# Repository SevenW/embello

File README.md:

Embedded software from JeeLabs
==============================

Quick Links
-----------

* [Home page and docs](http://embello.jeelabs.org/)
* [Forth-based JeeLabs JeeNodes Zero](./explore/1608-forth)

Acknowledgments
---------------

With many thanks for the inspiring discussions and code contributions by:

* James Churchill
* Thorsten von Eicken
* Martyn Judd
* Matthias Koch
* Thomas Lohmüller
* John O'Hare
* Joris Pragt
* Frank (SevenW)
* Matthias Ulrich

-- [jcw](http://jeelabs.org/about/)

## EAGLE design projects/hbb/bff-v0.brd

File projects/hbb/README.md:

See <http://jeelabs.org/2016/01/arduino-shields...-or-not/>

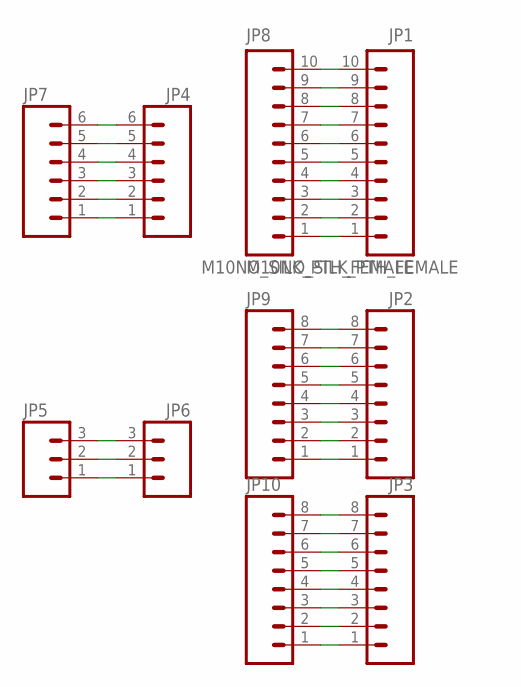
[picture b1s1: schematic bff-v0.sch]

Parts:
JP1, JP8: M10NO_SILK_PTH_FEMALE; 1X10_NO_SILK
JP2, JP3, JP9, JP10: M08NO_SILK_FEMALE_PTH; 1X08_NO_SILK
JP4, JP7: M06NO_SILK_FEMALE_PTH; 1X06_NO_SILK
JP5: M03LOCK_NO_SILK; 1X03_LOCK_NO_SILK
JP6: M03PTH; 1X03

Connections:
unnamed: JP5.1, JP6.1
unnamed: JP5.2, JP6.2
unnamed: JP5.3, JP6.3
unnamed: JP4.1, JP7.1
unnamed: JP4.2, JP7.2
unnamed: JP4.3, JP7.3
unnamed: JP4.4, JP7.4
unnamed: JP4.5, JP7.5
unnamed: JP4.6, JP7.6
unnamed: JP1.1, JP8.1
unnamed: JP1.2, JP8.2
unnamed: JP1.3, JP8.3
unnamed: JP1.4, JP8.4
unnamed: JP1.5, JP8.5
unnamed: JP1.6, JP8.6
unnamed: JP1.7, JP8.7
unnamed: JP1.8, JP8.8
unnamed: JP1.9, JP8.9
unnamed: JP1.10, JP8.10
unnamed: JP2.1, JP9.1
unnamed: JP2.2, JP9.2
unnamed: JP2.3, JP9.3
unnamed: JP2.4, JP9.4
unnamed: JP2.5, JP9.5
unnamed: JP2.6, JP9.6
unnamed: JP2.7, JP9.7
unnamed: JP2.8, JP9.8
unnamed: JP3.1, JP10.1
unnamed: JP3.2, JP10.2
unnamed: JP3.3, JP10.3
unnamed: JP3.4, JP10.4
unnamed: JP3.5, JP10.5
unnamed: JP3.6, JP10.6
unnamed: JP3.7, JP10.7
unnamed: JP3.8, JP10.8

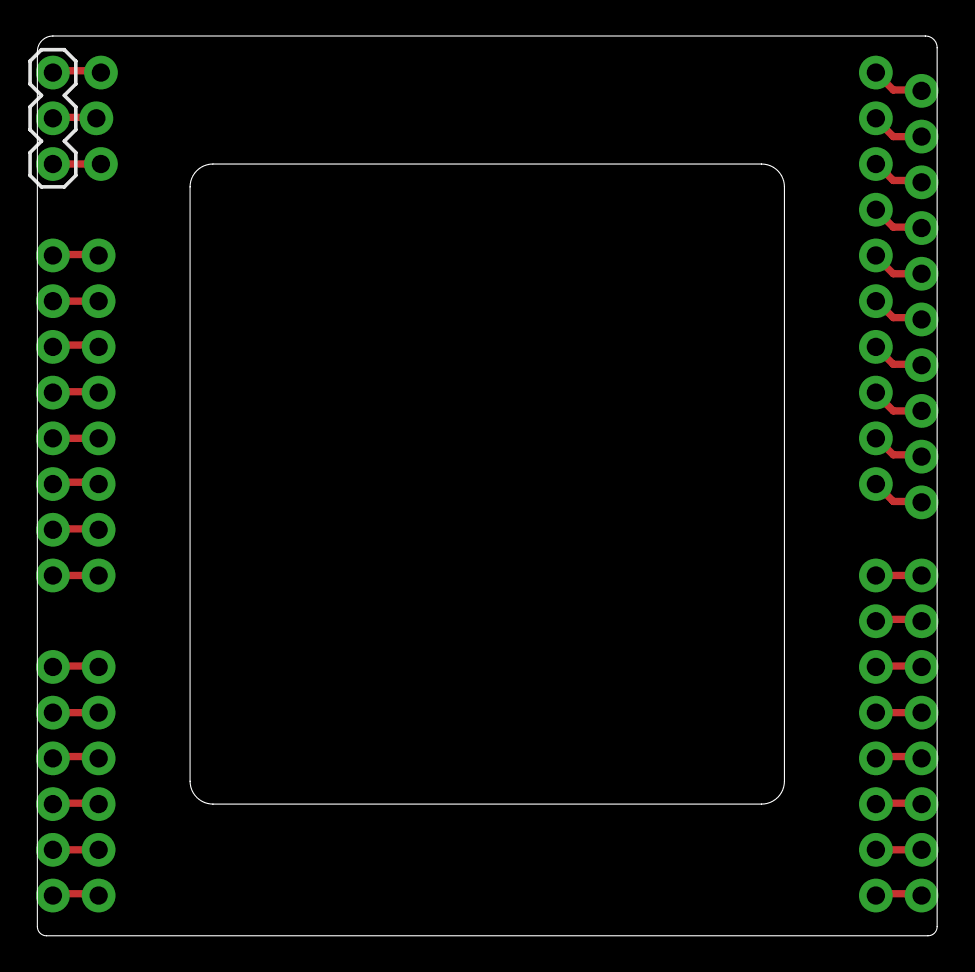
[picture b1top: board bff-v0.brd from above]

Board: 2 copper layers, 50.0 x 50.0 mm, 10 parts (0 on the bottom side), 35 nets.

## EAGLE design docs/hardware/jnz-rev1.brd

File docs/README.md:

This documentation can be viewed at <http://embello.jeelabs.org>.

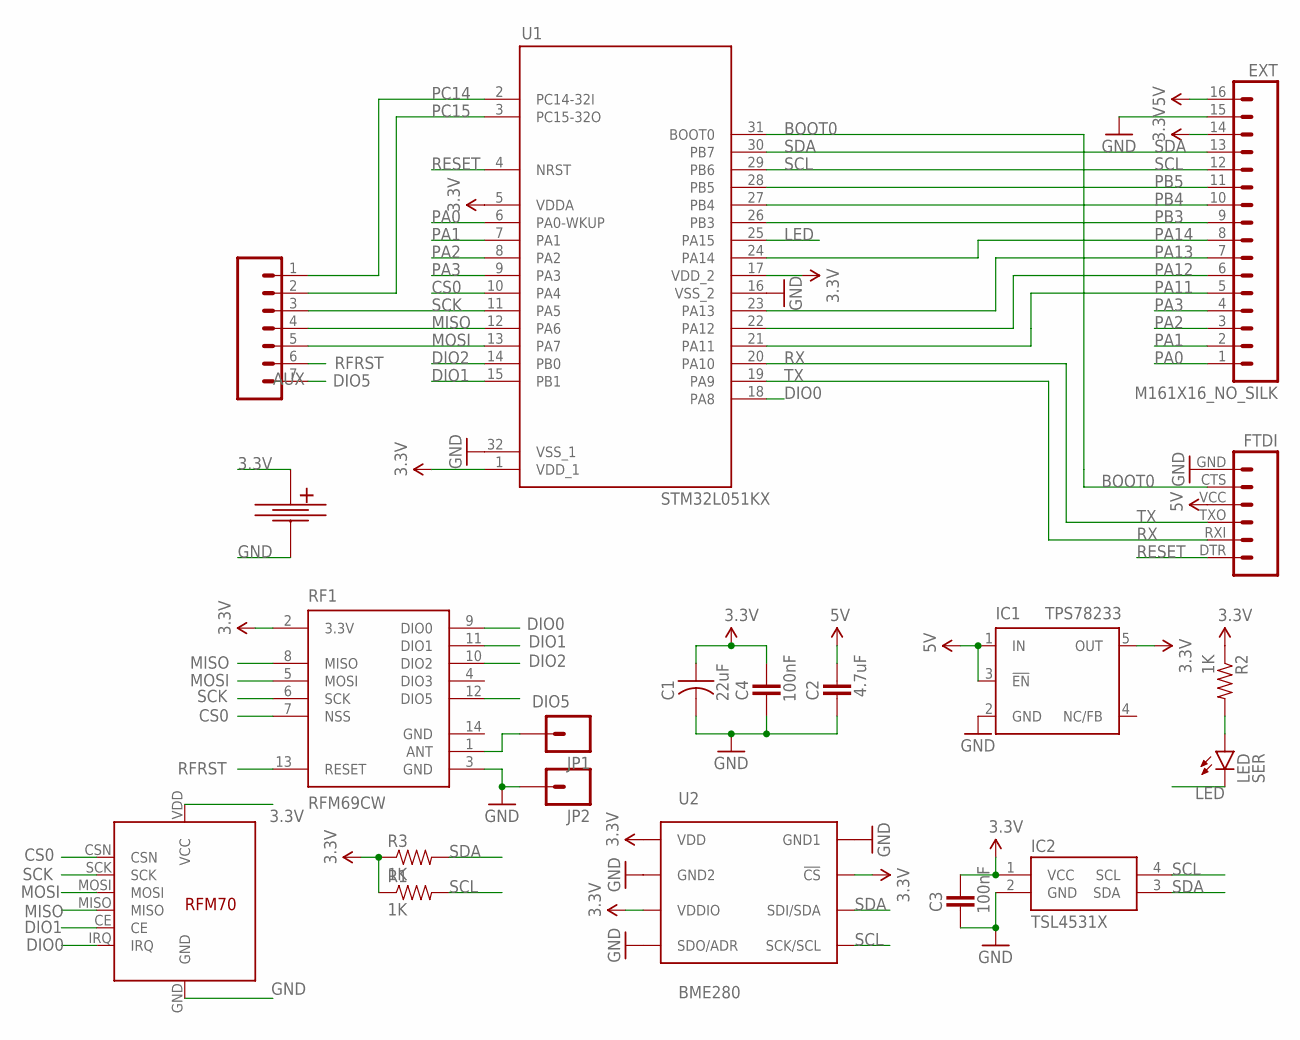
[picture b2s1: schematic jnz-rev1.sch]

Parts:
AUX: M07; 1X07
C1: 22uF; C0805
C2: 4.7uF; C0805K
C3, C4: 100nF; C0603K
EXT: M161X16_NO_SILK; 1X16_NO_SILK
FTDI: FTDI_BASICPTH; FTDI_BASIC
IC1: TPS78233; SOT23-DBV
IC2: TSL4531X; AMS_CL
JP1, JP2: M01NOSILK-KIT; 1X01NS-KIT
LED: SER; LED-0603
R1, R2, R3: 1K; 0603-RES
RF1: RFM69CW; RFM69CW-XXXS2
RF2: RFM7x; RFM70
U1: STM32L051KX; TQFP32-08
U2: BME280; BME280_LGA
U$2: CR2032-SMD

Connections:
3.3V: C1.1, C3.1, C4.1, EXT.14, IC1.5 (OUT), IC2.1 (VCC), R1.1, R2.1, R3.1, RF1.2 (3.3V), RF2.VDD (VCC), U1.1 (VDD_1), U1.5 (VDDA), U1.17 (VDD_2), U2.P$2 (!CS), U2.P$6 (VDDIO), U2.P$8 (VDD), U$2.POS (+)
5V: C2.1, EXT.16, FTDI.VCC (4), IC1.1 (IN), IC1.3 (!EN)
BOOT0: FTDI.CTS (5), U1.31 (BOOT0)
CS0: RF1.7 (NSS), RF2.CSN, U1.10 (PA4)
DIO0: RF1.9 (DIO0), RF2.IRQ, U1.18 (PA8)
DIO1: RF1.11 (DIO1), RF2.CE, U1.15 (PB1)
DIO2: RF1.10 (DIO2), U1.14 (PB0)
DIO5: AUX.7, RF1.12 (DIO5)
GND: C1.2, C2.2, C3.2, C4.2, EXT.15, FTDI.GND (6), IC1.2 (GND), IC2.2 (GND), JP2.1, RF1.3 (GND), RF1.14 (GND), RF2.GND, U1.16 (VSS_2), U1.32 (VSS_1), U2.P$1 (GND1), U2.P$5 (SDO/ADR), U2.P$7 (GND2), U$2.NEG (-)
LED: LED.C, U1.25 (PA15)
MISO: AUX.4, RF1.8 (MISO), RF2.MISO, U1.12 (PA6)
MOSI: AUX.5, RF1.5 (MOSI), RF2.MOSI, U1.13 (PA7)
unnamed: LED.A, R2.2
unnamed: JP1.1, RF1.1 (ANT)
PA0: EXT.1, U1.6 (PA0-WKUP)
PA1: EXT.2, U1.7 (PA1)
PA2: EXT.3, U1.8 (PA2)
PA3: EXT.4, U1.9 (PA3)
PA11: EXT.5, U1.21 (PA11)
PA12: EXT.6, U1.22 (PA12)
PA13: EXT.7, U1.23 (PA13)
PA14: EXT.8, U1.24 (PA14)
PB3: EXT.9, U1.26 (PB3)
PB4: EXT.10, U1.27 (PB4)
PB5: EXT.11, U1.28 (PB5)
PC14: AUX.1, U1.2 (PC14-32I)
PC15: AUX.2, U1.3 (PC15-32O)
RESET: FTDI.DTR (1), U1.4 (NRST)
RFRST: AUX.6, RF1.13 (RESET)
RX: FTDI.TXO (3), U1.20 (PA10)
SCK: AUX.3, RF1.6 (SCK), RF2.SCK, U1.11 (PA5)
SCL: EXT.12, IC2.4 (SCL), R1.2, U1.29 (PB6), U2.P$4 (SCK/SCL)
SDA: EXT.13, IC2.3 (SDA), R3.2, U1.30 (PB7), U2.P$3 (SDI/SDA)
TX: FTDI.RXI (2), U1.19 (PA9)

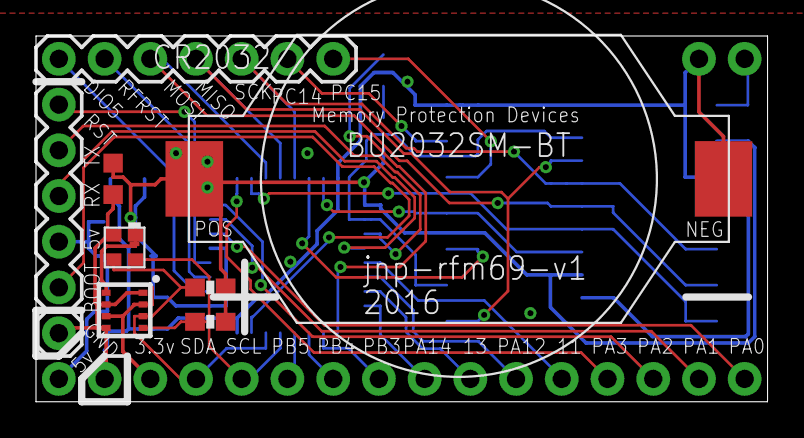
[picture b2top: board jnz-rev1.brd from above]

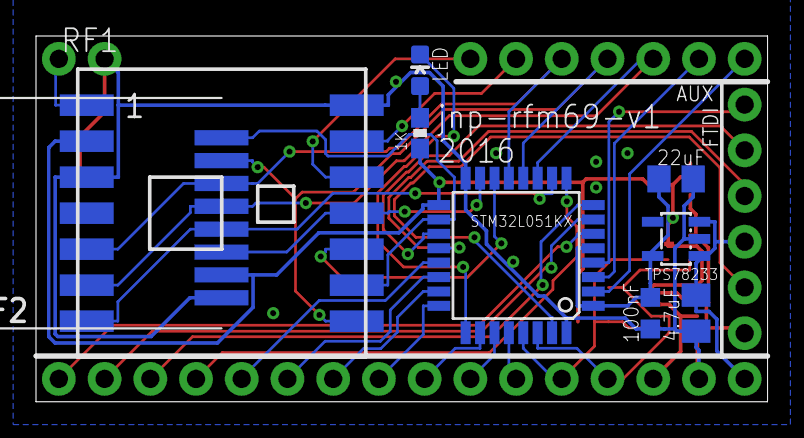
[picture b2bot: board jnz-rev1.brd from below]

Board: 2 copper layers, 40.6 x 20.3 mm, 20 parts (9 on the bottom side), 34 nets.

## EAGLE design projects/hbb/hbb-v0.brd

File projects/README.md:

In this folder:

**Arduino Sketch Collection** - <http://jeelabs.org/ask>

**Garage Parking Aid** - <http://jeelabs.org/gpa>

**Hy-Tiny Base Board** - <http://jeelabs.org/hbb>

**Micro Power Snitch** - <http://jeelabs.org/mps>

**RF Node Watcher** - <http://jeelabs.org/rnw>

**RasPi RF** - <http://jeelabs.org/rpr>

**Tinker Pico** - <http://jeelabs.org/tkp>

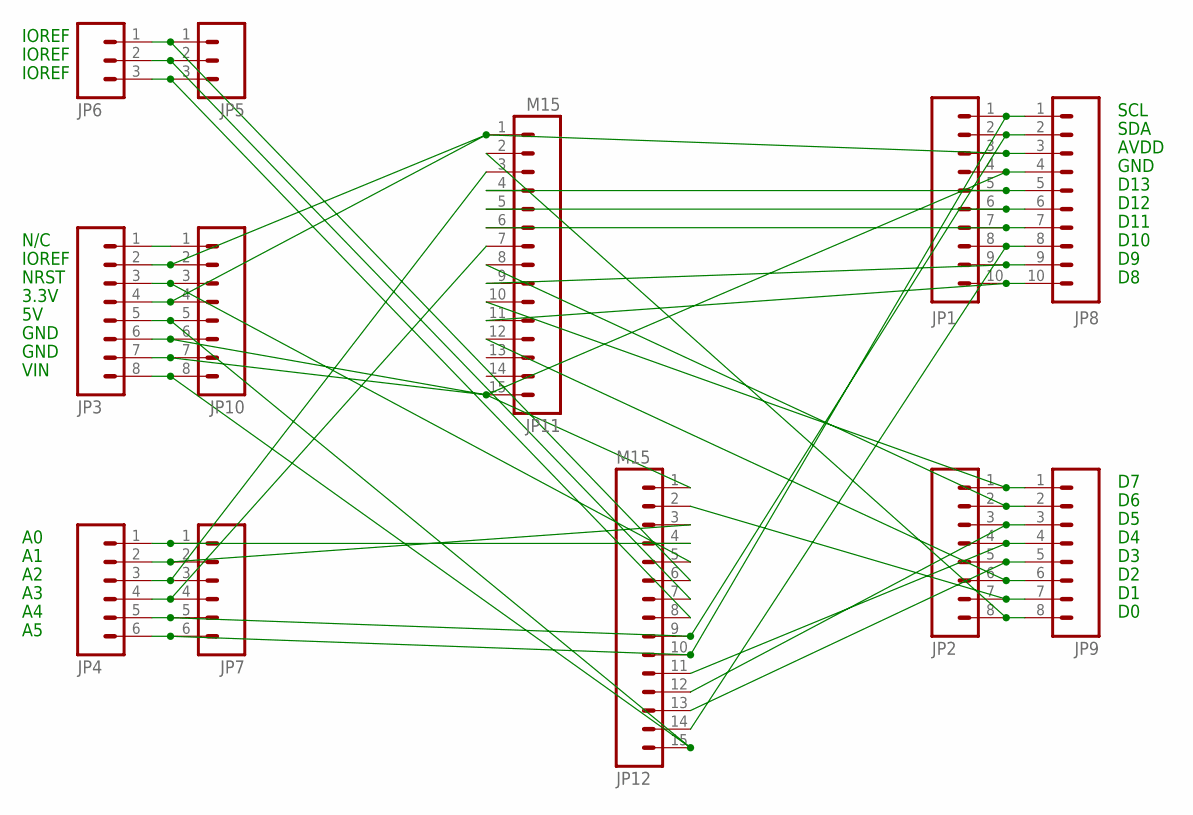
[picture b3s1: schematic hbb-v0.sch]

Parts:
JP1, JP8: M10NO_SILK_PTH_FEMALE; 1X10_NO_SILK
JP2, JP3, JP9, JP10: M08NO_SILK_FEMALE_PTH; 1X08_NO_SILK
JP4, JP7: M06NO_SILK_FEMALE_PTH; 1X06_NO_SILK
JP5: M03LOCK_NO_SILK; 1X03_LOCK_NO_SILK
JP6: M03PTH; 1X03
JP11, JP12: M15; 1X15

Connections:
GND: JP1.4, JP3.6, JP3.7, JP8.4, JP10.6, JP10.7, JP11.15, JP12.1
unnamed: JP5.1, JP6.1, JP12.6
unnamed: JP5.2, JP6.2, JP12.7
unnamed: JP5.3, JP6.3, JP12.8
unnamed: JP4.1, JP7.1, JP12.4
unnamed: JP4.2, JP7.2, JP12.3
unnamed: JP4.3, JP7.3, JP11.3
unnamed: JP4.4, JP7.4, JP11.7
unnamed: JP1.2, JP4.5, JP7.5, JP8.2, JP12.9
unnamed: JP1.1, JP4.6, JP7.6, JP8.1, JP12.10
unnamed: JP1.5, JP8.5, JP11.4
unnamed: JP1.6, JP8.6, JP11.5
unnamed: JP1.7, JP8.7, JP11.6
unnamed: JP1.8, JP8.8, JP12.14
unnamed: JP1.9, JP8.9, JP11.9
unnamed: JP1.10, JP8.10, JP11.11
unnamed: JP2.1, JP9.1, JP11.10
unnamed: JP2.2, JP9.2, JP11.8
unnamed: JP2.3, JP9.3, JP12.12
unnamed: JP2.4, JP9.4, JP12.11
unnamed: JP2.5, JP9.5, JP12.13
unnamed: JP2.6, JP9.6, JP11.12
unnamed: JP2.7, JP9.7, JP12.2
unnamed: JP2.8, JP9.8, JP11.2
unnamed: JP3.1, JP10.1
unnamed: JP1.3, JP3.2, JP3.4, JP8.3, JP10.2, JP10.4, JP11.1
unnamed: JP3.3, JP10.3, JP12.5
unnamed: JP3.5, JP3.8, JP10.5, JP10.8, JP12.15

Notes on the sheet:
N/C
IOREF
NRST
3.3V
GND
VIN
SCL
SDA
AVDD
D13
D12
D11
D10

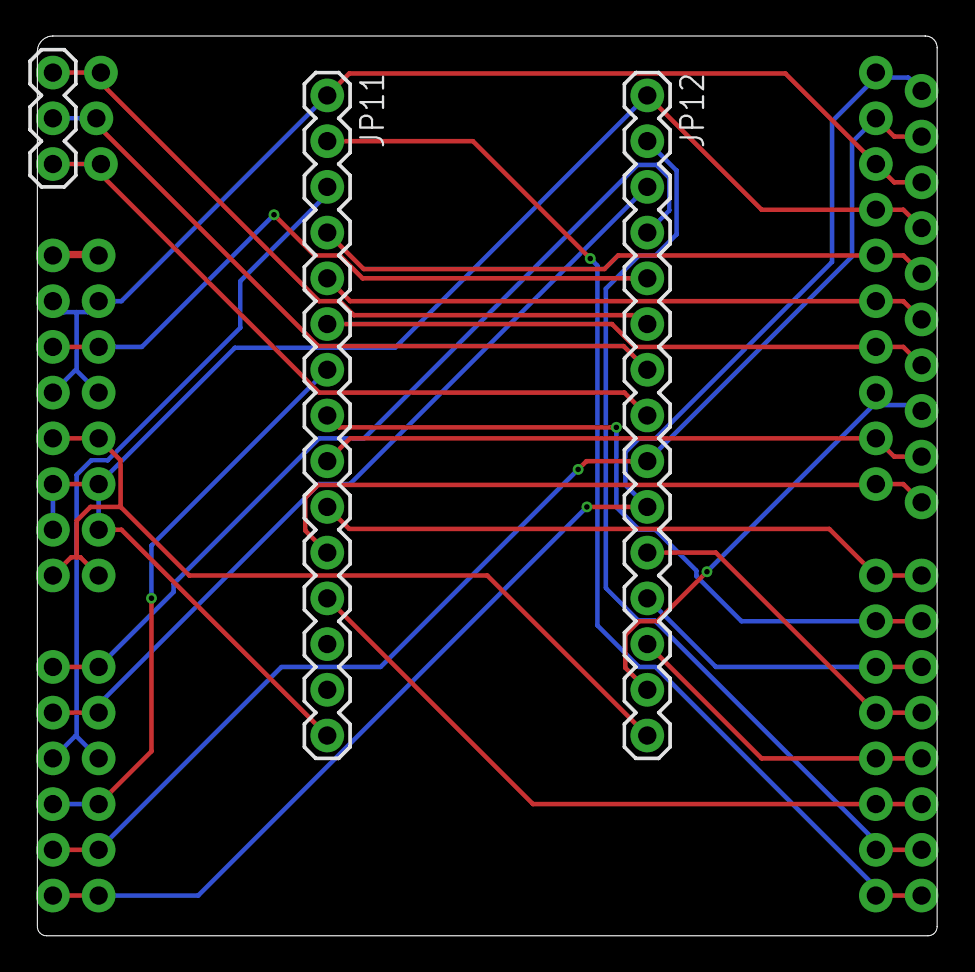
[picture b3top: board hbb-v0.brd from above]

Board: 2 copper layers, 50.0 x 50.0 mm, 12 parts (0 on the bottom side), 28 nets.

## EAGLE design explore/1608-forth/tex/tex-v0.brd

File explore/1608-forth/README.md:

A collection of files for use with Mecrisp Stellaris Forth on STM32 boards. See
[this article](http://jeelabs.org/2016/06/thoughts-about-app-structure/) for the
structure of these directories, and how source files should be loaded:

* **`bct`** - Blue Pill Component Tester, explores the ADC & GPIO pins
* **`bme`** - BME280 sensor exploration using the Olimexino-STM32
* **`cag`** - Console Access Gateway w/ STM32F103, acting as central RF console
* **`eee`** - Experimental Engine Explorations on a HyTiny
* **`g6s`** - Generic 64-pin F103 chips for use with the serial port (USART1)
* **`g6u`** - Generic 64-pin F103 chips for use with USB console driver
* **`i2c`** - I2C test setup with lots of breakout boards and JeeLabs plugs
* **`lnr`** - Led Node Revisited - using a JeeNode Zero to drive LEDs via PWM
* **`prc`** - Pico Reflow Controller w/ HyTiny, OLED, MOSFET, RFM69, 12-24V Vin
* **`qld`** - Quick Loader -  using a Blue Pill to  re-flash a JNZ via SPI
* **`rfc`** - Remote Console driver, routes console I/O over RF
* **`rvm`** - Remote voltmeter w/ STM32L052 and a 4-chan Analog Plug
* **`sic`** - Soldering Iron Controller
* **`suf`** - Serial USB driver for Forth, routes console I/O over USB
* **`ten`** - Test Echo Node, used for testing JeeNode Zero boards
* **`tex`** - Tiny Extender, a HyTiny w/ extender board for RFM69 + SPI flash
* **`trf`** - Tiny RF node, a bridge from RFM69 to USB serial
* **`zeb`** - STM32F103ZE "Basic" board w/ µSD and two 2x32-pin headers

These files implement a range of hardware drivers and other generic functions:

* **`flib`** - Forth library, various modules used by the above boards
* **`flib/mecrisp`** - Mecrisp library, copied / modified from Mecrisp code

Most of the above projects use Mecrisp Forth "core" builds from this area:

* **`cores`** - Matthias Koch's Mecrisp Stellaris Forth with minor extensions

The following older projects use files called `h` (hardware), `l` (library), and
`d` (development), which should be loaded in that order. However, due to changes
elsewhere, it is very likely that they won't work as is anymore, as of 2017.

* **`aia`** - ARMinARM, Raspberry add-on w/ STM32F103RE
* **`cbf`** - Haoyu Core Board Four board w/ STM32F407ZG and lots of RAM+flash
* **`cbo`** - Haoyu Core Board One board w/ STM32F103ZE and lots of RAM+flash
* **`dad`** - Dime-A-Dozen, for all those cheap eBay STM32F103C8 boards
* **`gd4`** - GoldDragon 407 w/ STM32F407ZG and 3.2" LCD
* **`hmv`** - Haoyu Hy-STM32MiniV board w/ STM32F103VC and 3.2" LCD
* **`kb7`** - Ken Boak's STM32F746VG Break-Out-Board
* **`lsd`** - Little Shark Display board w/ STM32F107RC and 1.44" LCD
* **`mrn`** - Multi Receiver Node w/ STM32F103C8 and some wireless modules
* **`oxs`** - Olimexino-STM32 board w/ STM32F103RB, CAN, µSD, and LiPo charger
* **`rnw`** - RF Node Watcher w/ HyTiny STM32F103TB, RFM69, and 128x64 OLED
* **`wpz`** - WaveShare Port103Z w/ STM32F103ZE
* **`ybc`** - Yellow Blue STM32F103VC board
* **`ztw`** - Zero To Wireless demo w/ STM32F103C8 "Blue Pill" and RFM69CW

For more details, see the JeeLabs weblog posts and articles:

* <http://jeelabs.org/2016/02/dive-into-forth/>
* <http://jeelabs.org/2016/03/dive-into-forth-part-2/>
* <http://jeelabs.org/2016/03/dive-into-forth-part-3/>

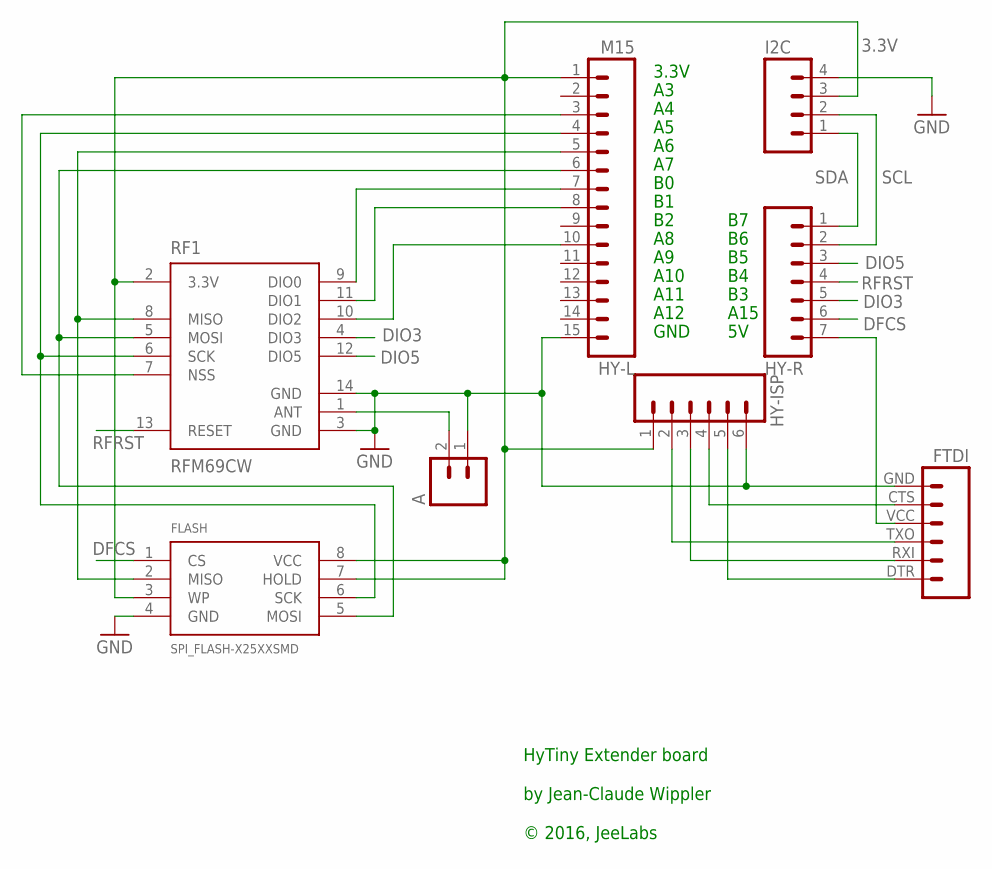
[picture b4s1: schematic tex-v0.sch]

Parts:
A: M021X02_NO_SILK; 1X02_NO_SILK
FLASH: SPI_FLASH-X25XXSMD; SO08
FTDI: FTDI_BASICPTH; FTDI_BASIC
HY-ISP: M06NO_SILK_FEMALE_PTH; 1X06_NO_SILK
HY-L: M15; 1X15
HY-R: M07; 1X07
I2C: M041X04_NO_SILK; 1X04_NO_SILK
RF1: RFM69CW; RFM69CW-XXXS2

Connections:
3.3V: FLASH.3 (WP), FLASH.7 (HOLD), FLASH.8 (VCC), HY-ISP.1, HY-L.1, I2C.3, RF1.2 (3.3V)
DFCS: FLASH.1 (CS), HY-R.6
DIO3: HY-R.5, RF1.4 (DIO3)
DIO5: HY-R.3, RF1.12 (DIO5)
GND: A.1, FLASH.4 (GND), FTDI.GND (6), HY-ISP.6, HY-L.15, I2C.4, RF1.3 (GND), RF1.14 (GND)
unnamed: FLASH.2 (MISO), HY-L.5, RF1.8 (MISO)
unnamed: FLASH.5 (MOSI), HY-L.6, RF1.5 (MOSI)
unnamed: FLASH.6 (SCK), HY-L.4, RF1.6 (SCK)
unnamed: HY-L.3, RF1.7 (NSS)
unnamed: FTDI.VCC (4), HY-R.7
unnamed: HY-L.7, RF1.9 (DIO0)
unnamed: HY-L.8, RF1.11 (DIO1)
unnamed: A.2, RF1.1 (ANT)
unnamed: FTDI.RXI (2), HY-ISP.3
unnamed: FTDI.TXO (3), HY-ISP.2
unnamed: FTDI.CTS (5), HY-ISP.4
unnamed: FTDI.DTR (1), HY-ISP.5
unnamed: HY-L.10, RF1.10 (DIO2)
RFRST: HY-R.4, RF1.13 (RESET)
SCL: HY-R.2, I2C.2
SDA: HY-R.1, I2C.1

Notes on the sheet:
3.3V
A10
A11
A12
GND
A15
HyTiny Extender board by Jean-Claude Wippler © 2016, JeeLabs

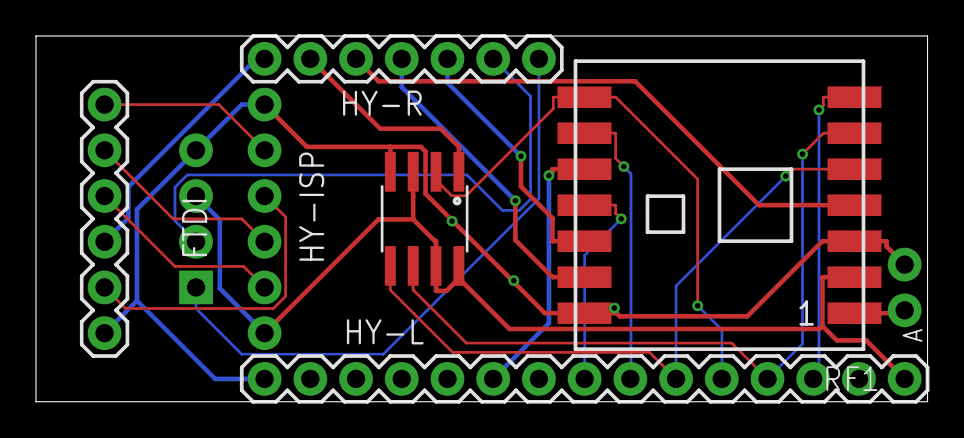
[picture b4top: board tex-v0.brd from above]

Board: 2 copper layers, 49.5 x 20.3 mm, 8 parts (1 on the bottom side), 21 nets.

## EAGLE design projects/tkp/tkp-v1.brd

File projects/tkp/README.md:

# Tinker Pico

The "Tinker Pico" is a breakout board for the 32-bit LPC824 microcontroller.  
It includes a 5V -> 3.3V regulator and an FTDI-compatible header for uploading.

See <http://jeelabs.org/tkp> for details.

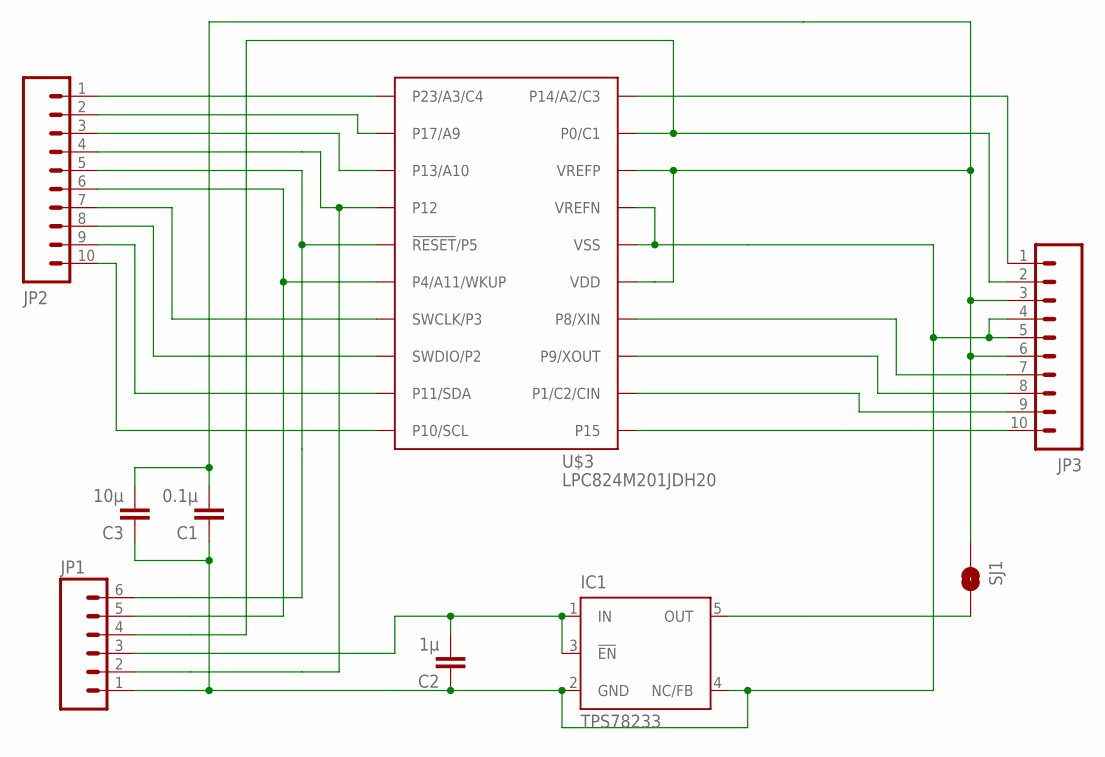
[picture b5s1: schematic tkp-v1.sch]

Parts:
C1: 0.1µ; C0603K
C2: 1µ; C0603K
C3: 10µ; C0805K
IC1: TPS78233; SOT23-DBV
JP1: M06LONGPADS; 1X06_LONGPADS
JP2, JP3: M10NO_SILK_PTH_FEMALE; 1X10_NO_SILK
SJ1: SOLDERJUMPERTRACE; SJ_2S-TRACE
U$3: LPC824M201JDH20; TSSOP20

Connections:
GND: C1.1, C2.1, C3.1, IC1.2 (GND), IC1.4 (NC/FB), JP1.1, JP3.4, JP3.5, U$3.16 (VSS), U$3.17 (VREFN)
unnamed: JP2.1, U$3.1 (P23/A3/C4)
unnamed: C2.2, IC1.1 (IN), IC1.3 (!EN), JP1.3
unnamed: JP1.4, JP3.2, U$3.19 (P0/C1)
unnamed: C1.2, C3.2, JP3.3, JP3.6, SJ1.1, U$3.15 (VDD), U$3.18 (VREFP)
unnamed: JP1.5, JP2.6, U$3.6 (P4/A11/WKUP)
unnamed: JP2.2, U$3.2 (P17/A9)
unnamed: JP3.1, U$3.20 (P14/A2/C3)
unnamed: JP3.7, U$3.14 (P8/XIN)
unnamed: JP3.8, U$3.13 (P9/XOUT)
unnamed: JP3.9, U$3.12 (P1/C2/CIN)
unnamed: JP3.10, U$3.11 (P15)
unnamed: JP1.2, JP2.4, U$3.4 (P12)
unnamed: JP2.3, U$3.3 (P13/A10)
unnamed: JP1.6, JP2.5, U$3.5 (!RESET!/P5)
unnamed: IC1.5 (OUT), SJ1.2
unnamed: JP2.7, U$3.7 (SWCLK/P3)
unnamed: JP2.8, U$3.8 (SWDIO/P2)
unnamed: JP2.9, U$3.9 (P11/SDA)
unnamed: JP2.10, U$3.10 (P10/SCL)

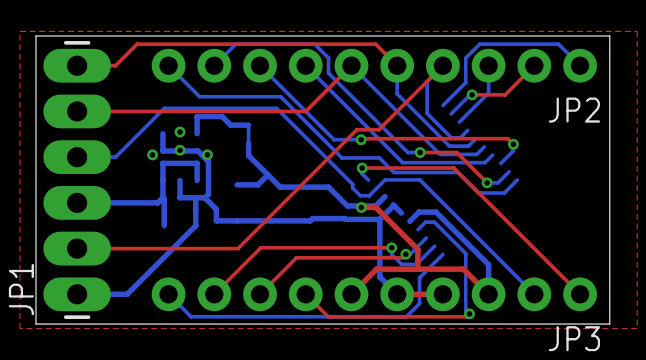
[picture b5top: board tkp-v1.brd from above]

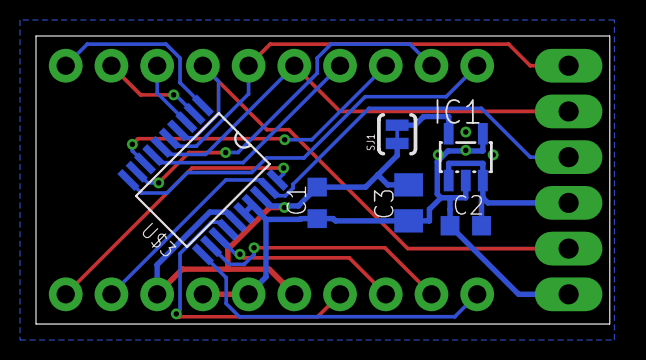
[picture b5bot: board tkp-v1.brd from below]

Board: 2 copper layers, 31.9 x 16.0 mm, 9 parts (6 on the bottom side), 20 nets.

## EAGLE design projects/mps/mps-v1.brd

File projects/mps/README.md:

# Micro Power Snitch

The "Micro Power Snitch" is a battery-less circuit which sends out wireless
data packets using energy harvested from a Current Transformer, for example.

See <http://jeelabs.org/mps> for details.

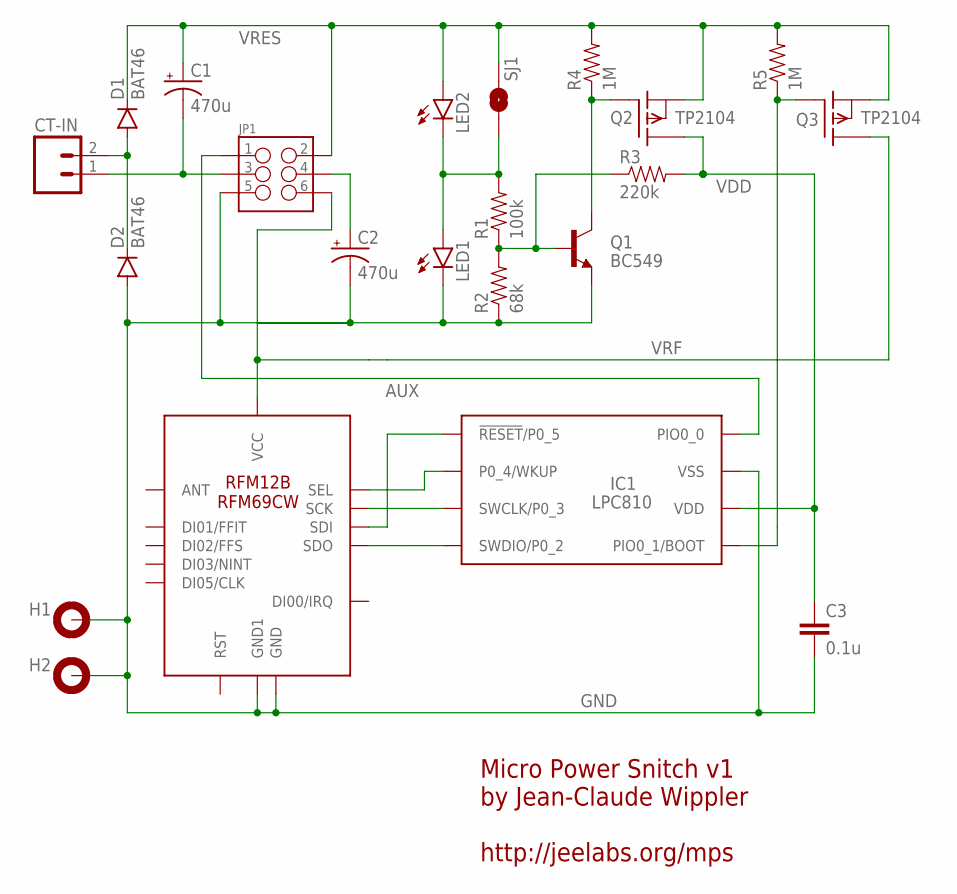
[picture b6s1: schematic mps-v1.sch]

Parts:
C1, C2: 470u; CPOL-RADIAL-100UF-25V
C3: 0.1u; CAP-PTH-SMALL
CT-IN: M023.5MM; SCREWTERMINAL-3.5MM-2
D1, D2: BAT46; DIODE-1N4148
H1, H2: MOUNT-PAD-ROUND2.8; 2,8-PAD
IC1: LPC810; DIP8
JP1: M03X2NO_SILK; 2X3-NS
LED1, LED2: LED3MM
Q1: BC549; TO92
Q2, Q3: TP2104; TO92
R1: 100k; AXIAL-0.3
R2: 68k; AXIAL-0.3
R3: 220k; AXIAL-0.3
R4, R5: 1M; AXIAL-0.3
RFM12B/69CW: RFM12B/69CW
SJ1: JUMPER-PAD-2-NO; PAD-JUMPER-2-NO_NO_SILK

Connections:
AUX: IC1.P$8 (PIO0_0), JP1.1
GND: C2.2 (-), C3.2, D2.A, H1.B2,8, H2.B2,8, IC1.P$7 (VSS), JP1.5, LED1.K (C), Q1.1 (E), R2.P$1 (1), RFM12B/69CW.GND, RFM12B/69CW.GND1
unnamed: CT-IN.2, D1.A, D2.C
unnamed: C2.1 (+), JP1.4
unnamed: IC1.P$3 (SWCLK/P0_3), RFM12B/69CW.SCK
unnamed: C1.2 (-), CT-IN.1, JP1.3
unnamed: LED1.A, LED2.K (C), R1.P$2 (2), SJ1.1
unnamed: Q1.3 (C), Q2.2 (G), R4.P$1 (1)
unnamed: Q1.2 (B), R1.P$1 (1), R2.P$2 (2), R3.P$1 (1)
unnamed: IC1.P$1 (!RESET!/P0_5), RFM12B/69CW.SDI
unnamed: IC1.P$2 (P0_4/WKUP), RFM12B/69CW.SEL
unnamed: IC1.P$4 (SWDIO/P0_2), RFM12B/69CW.SDO
unnamed: IC1.P$5 (PIO0_1/BOOT), Q3.2 (G), R5.P$1 (1)
VDD: C3.1, IC1.P$6 (VDD), Q2.3 (D), R3.P$2 (2)
VRES: C1.1 (+), D1.C, JP1.2, LED2.A, Q2.1 (S), Q3.1 (S), R4.P$2 (2), R5.P$2 (2), SJ1.2
VRF: JP1.6, Q3.3 (D), RFM12B/69CW.VDD (VCC)

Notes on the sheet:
Micro Power Snitch v1 by Jean-Claude Wippler http://jeelabs.org/mps

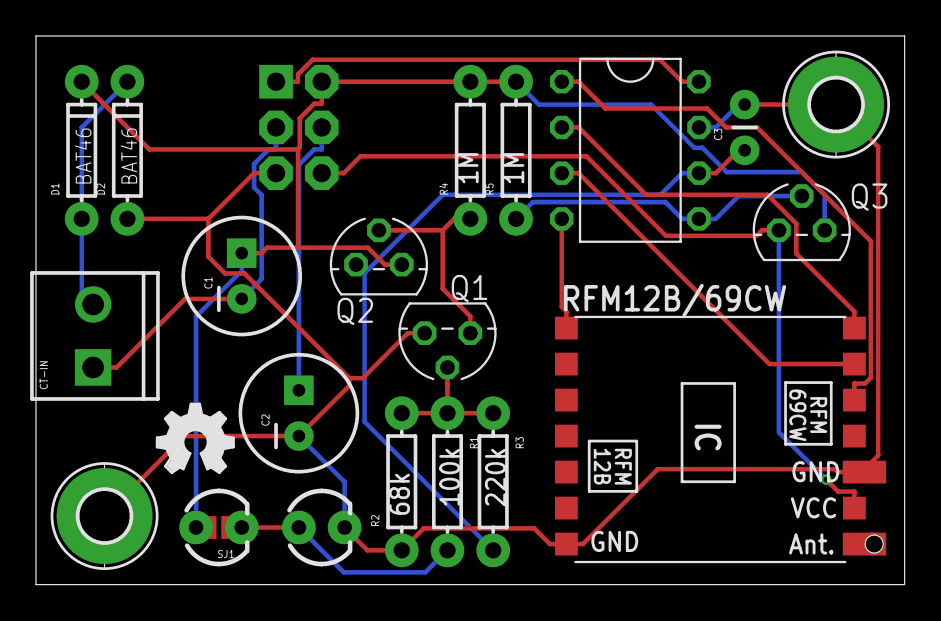
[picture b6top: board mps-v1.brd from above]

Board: 2 copper layers, 48.3 x 30.5 mm, 23 parts (0 on the bottom side), 16 nets.

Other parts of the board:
LOGO1: OSHW_LOGO_FILLX0150-NT; OSHW_FILLX150_NOTEXT

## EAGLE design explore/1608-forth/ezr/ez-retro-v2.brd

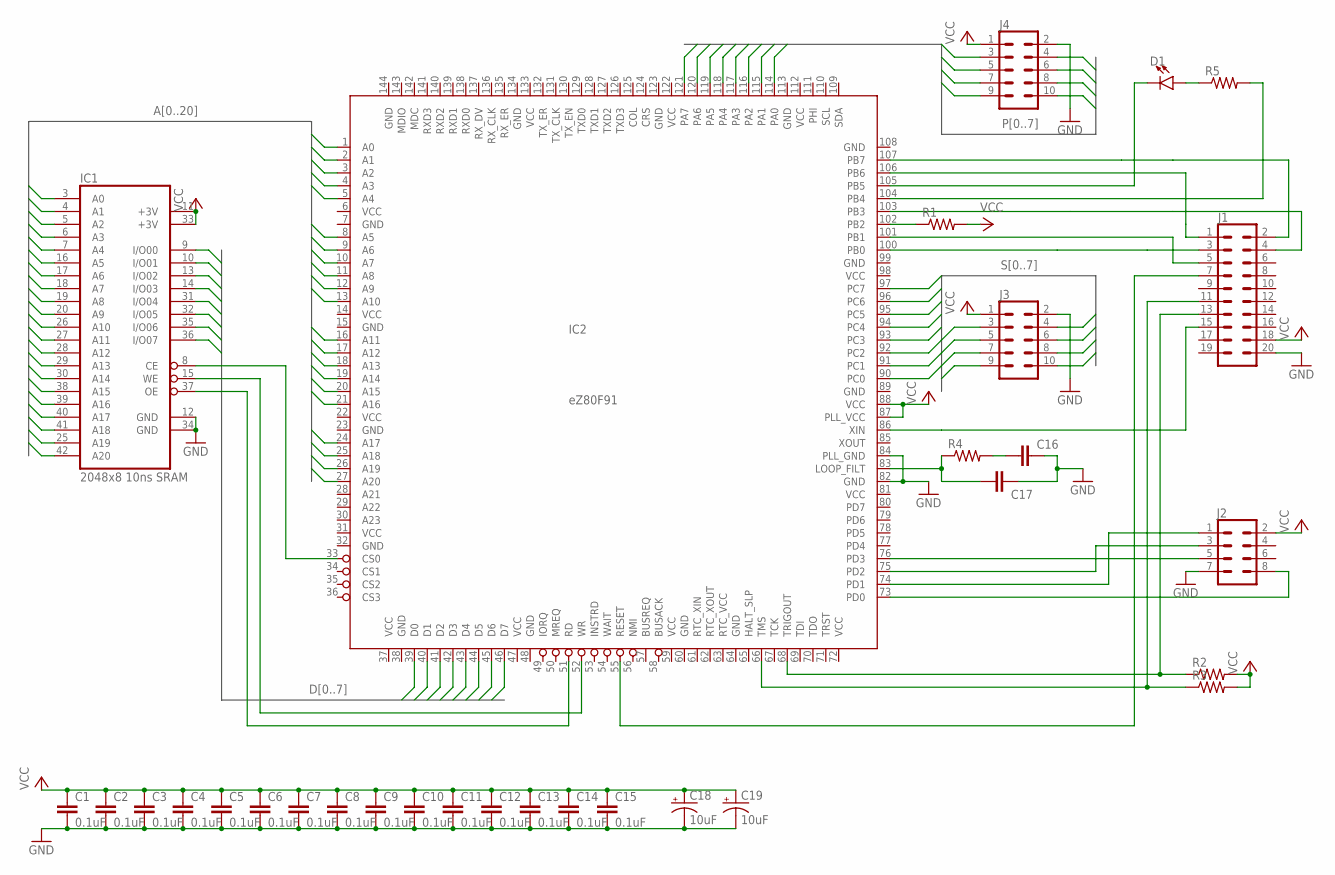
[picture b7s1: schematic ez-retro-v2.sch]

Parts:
C1, C2, C3, C4, C5, C6, C7, C8, C9, C10, C11, C12, C13, C14, C15, C16, C17: 0.1uF; 0603
C18, C19: 10uF; EIA3216
D1: LED1206; LED-1206
IC1: 2048x8 10ns SRAM; TSOPII-Z44
IC2: eZ80F91; TQFP144
J1: CONN_10X2NOSILK; 2X10_NOSILK
J2: CONN_04X2; 2X4
J3, J4: CONN_05X2NO_SILK; 2X5_NOSILK
R1, R2, R3, R4, R5: RESISTOR0603-RES; 0603-RES

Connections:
A0: IC1.3 (A0), IC2.1 (A0)
A1: IC1.4 (A1), IC2.2 (A1)
A2: IC1.5 (A2), IC2.3 (A2)
A3: IC1.6 (A3), IC2.4 (A3)
A4: IC1.7 (A4), IC2.5 (A4)
A5: IC1.16 (A5), IC2.8 (A5)
A6: IC1.17 (A6), IC2.9 (A6)
A7: IC1.18 (A7), IC2.10 (A7)
A8: IC1.19 (A8), IC2.11 (A8)
A9: IC1.20 (A9), IC2.12 (A9)
A10: IC1.26 (A10), IC2.13 (A10)
A11: IC1.27 (A11), IC2.16 (A11)
A12: IC1.28 (A12), IC2.17 (A12)
A13: IC1.29 (A13), IC2.18 (A13)
A14: IC1.30 (A14), IC2.19 (A14)
A15: IC1.38 (A15), IC2.20 (A15)
A16: IC1.39 (A16), IC2.21 (A16)
A17: IC1.40 (A17), IC2.24 (A17)
A18: IC1.41 (A18), IC2.25 (A18)
A19: IC1.25 (A19), IC2.26 (A19)
A20: IC1.42 (A20), IC2.27 (A20)
D0: IC1.9 (I/O00), IC2.39 (D0)
D1: IC1.10 (I/O01), IC2.40 (D1)
D2: IC1.13 (I/O02), IC2.41 (D2)
D3: IC1.14 (I/O03), IC2.42 (D3)
D4: IC1.31 (I/O04), IC2.43 (D4)
D5: IC1.32 (I/O05), IC2.44 (D5)
D6: IC1.35 (I/O06), IC2.45 (D6)
D7: IC1.36 (I/O07), IC2.46 (D7)
GND: C1.2, C2.2, C3.2, C4.2, C5.2, C6.2, C7.2, C8.2, C9.1, C10.2, C11.2, C12.2, C13.2, C14.2, C15.2, C16.2, C17.2, C18.-, C19.-, IC1.12 (GND), IC1.34 (GND), IC2.7 (GND), IC2.15 (GND), IC2.23 (GND), IC2.32 (GND), IC2.38 (GND), IC2.48 (GND), IC2.60 (GND), IC2.64 (GND), IC2.82 (GND), IC2.84 (PLL_GND), IC2.89 (GND), IC2.99 (GND), IC2.108 (GND), IC2.113 (GND), IC2.123 (GND), IC2.134 (GND), J1.20, J2.7, J3.2, J4.2
unnamed: IC1.37 (OE), IC2.51 (RD)
unnamed: IC1.15 (WE), IC2.52 (WR)
unnamed: IC1.8 (CE), IC2.33 (CS0)
unnamed: IC2.100 (PB0), J1.3
unnamed: IC2.106 (PB6), J1.1
unnamed: IC2.103 (PB3), J1.4
unnamed: IC2.107 (PB7), J1.2
unnamed: IC2.86 (XIN), J1.15
unnamed: IC2.55 (RESET), J1.7
unnamed: IC2.101 (PB1), J1.5
unnamed: IC2.66 (TMS), J1.11, R3.1
unnamed: IC2.102 (PB2), R1.1
unnamed: IC2.68 (TRIGOUT), J1.13, R2.1
unnamed: IC2.74 (PD1), J2.1
unnamed: IC2.73 (PD0), J2.8
unnamed: IC2.76 (PD3), J2.5
unnamed: IC2.75 (PD2), J2.3
unnamed: C17.1, IC2.83 (LOOP_FILT), R4.1
unnamed: C16.1, R4.2
unnamed: D1.A, R5.1
unnamed: D1.C, IC2.105 (PB5)
unnamed: IC2.104 (PB4), R5.2
P0: IC2.114 (PA0), J4.3
P1: IC2.115 (PA1), J4.4
P2: IC2.116 (PA2), J4.5
P3: IC2.117 (PA3), J4.6
P4: IC2.118 (PA4), J4.7
P5: IC2.119 (PA5), J4.8
P6: IC2.120 (PA6), J4.9
P7: IC2.121 (PA7), J4.10
RTC_VCC: IC2.63 (RTC_VCC)
S0: IC2.90 (PC0), J3.3
S1: IC2.91 (PC1), J3.4
S2: IC2.92 (PC2), J3.5
S3: IC2.93 (PC3), J3.6
S4: IC2.94 (PC4), J3.7
S5: IC2.95 (PC5), J3.8
S6: IC2.96 (PC6), J3.9
S7: IC2.97 (PC7), J3.10
VCC: C1.1, C2.1, C3.1, C4.1, C5.1, C6.1, C7.1, C8.1, C9.2, C10.1, C11.1, C12.1, C13.1, C14.1, C15.1, C18.+, C19.+, IC1.11 (+3V), IC1.33 (+3V), IC2.6 (VCC), IC2.14 (VCC), IC2.22 (VCC), IC2.31 (VCC), IC2.37 (VCC), IC2.47 (VCC), IC2.59 (VCC), IC2.72 (VCC), IC2.81 (VCC), IC2.87 (PLL_VCC), IC2.88 (VCC), IC2.98 (VCC), IC2.112 (VCC), IC2.122 (VCC), IC2.133 (VCC), J1.18, J2.2, J3.1, J4.1, R1.2, R2.2, R3.2
WP: IC2.144 (WP)

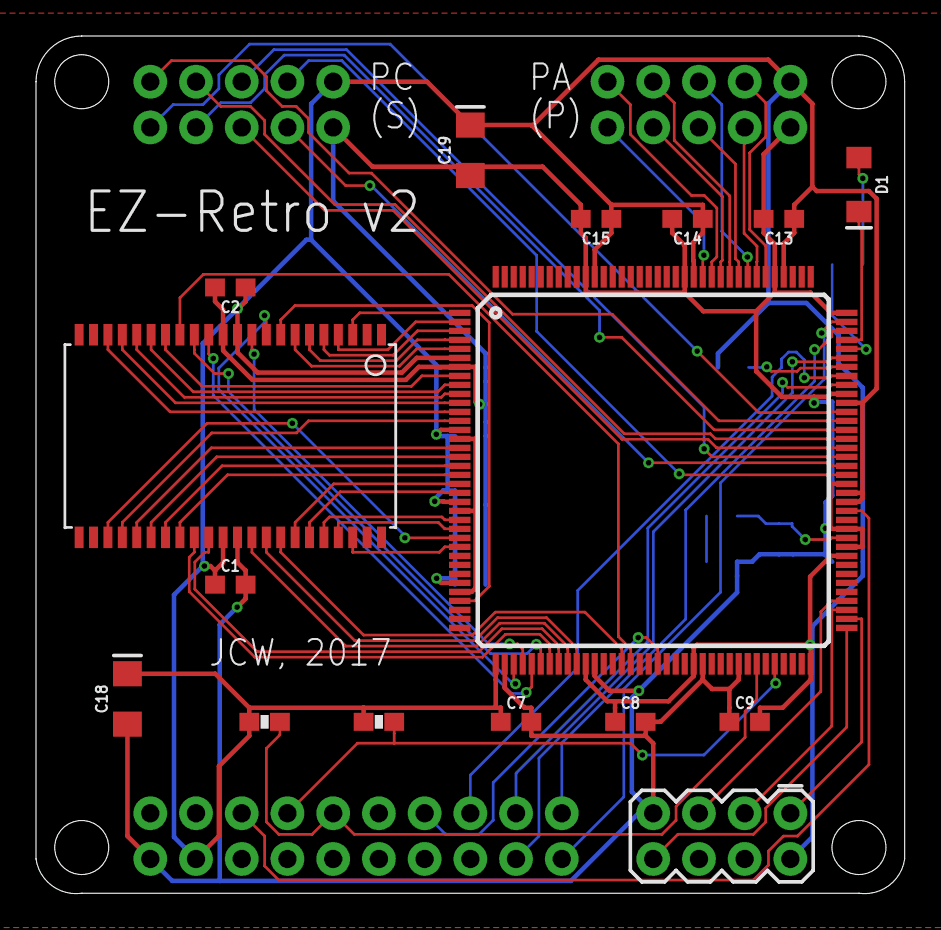
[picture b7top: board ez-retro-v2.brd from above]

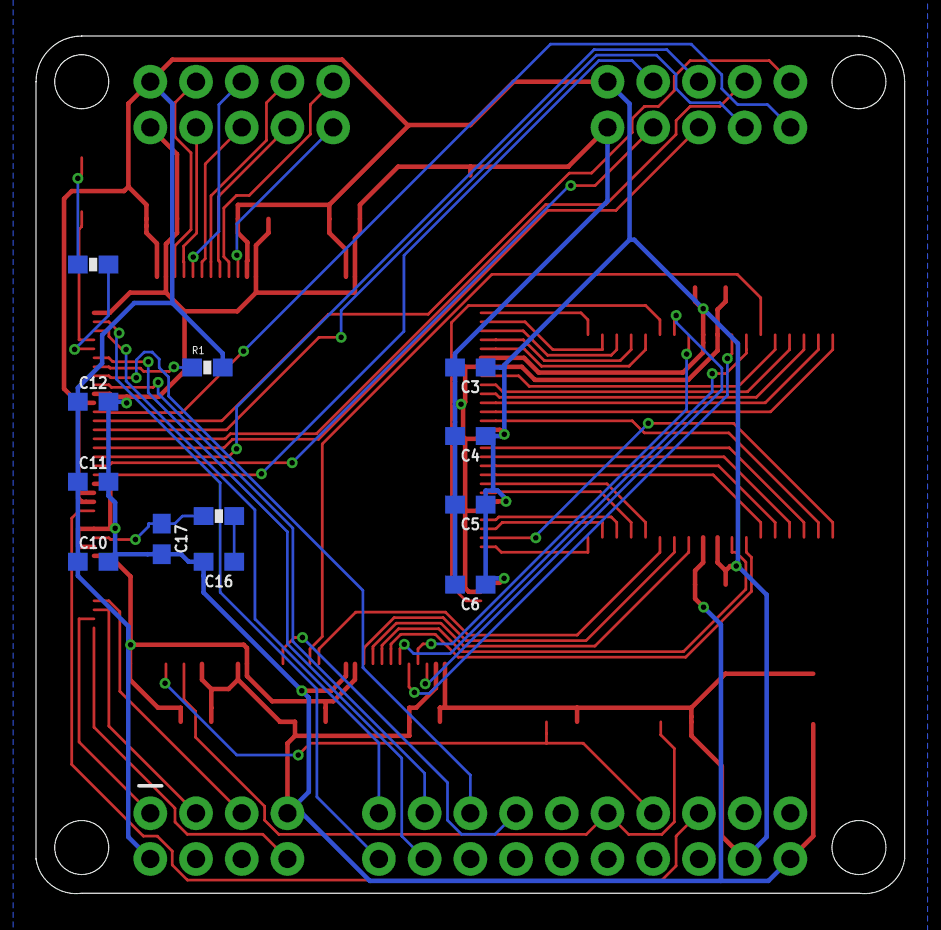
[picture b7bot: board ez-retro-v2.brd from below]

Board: 2 copper layers, 48.3 x 47.6 mm, 31 parts (12 on the bottom side), 69 nets.

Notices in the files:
parts and their libraries:
SparkFun-Connectors: Licensing: Creative Commons ShareAlike 4.0 International - https://creativecommons.org/licenses/by-sa/4.0
